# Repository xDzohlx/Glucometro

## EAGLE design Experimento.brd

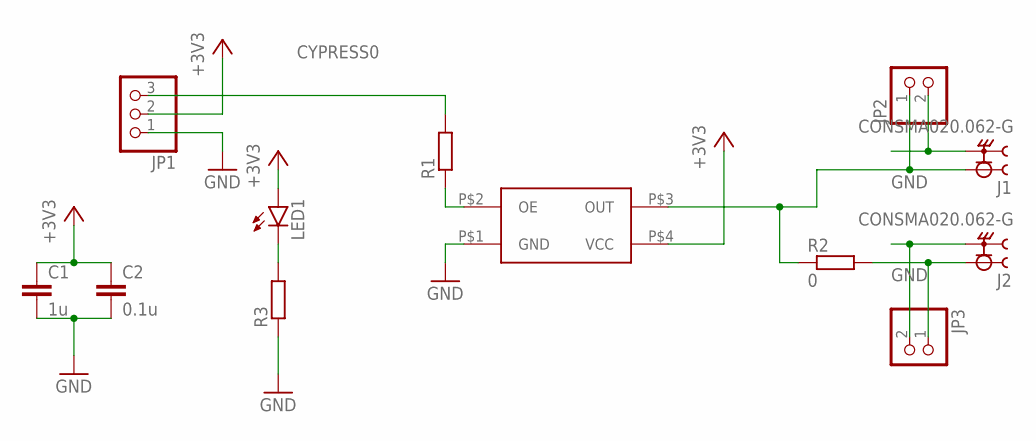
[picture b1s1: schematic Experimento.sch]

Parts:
C1: 1u; C0805
C2: 0.1u; C0805
J1, J2: CONSMA020.062-G; LINX_CONSMA020.062-G
JP1: PINHD-1X3; 1X03
JP2, JP3: PINHD-1X2M; 1X02M
LED1: LEDSML0603; SML0603
R1: R-EU_R0603; R0603
R2: 0; R1206
R3: R-EU_R0805; R0805
U$1: 732-XG1000CA100CBL3

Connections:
+3V3: C1.1, C2.1, JP1.2, LED1.A, U$1.P$4 (VCC)
CYPRESS0: JP1.3, R1.2
GND: C1.2, C2.2, J1.S1 (2), J1.S2 (2), J1.S3 (2), J1.S4 (2), J2.S1 (2), J2.S2 (2), J2.S3 (2), J2.S4 (2), JP1.1, JP2.2, JP3.2, R3.1, U$1.P$1 (GND)
unnamed: J2.1, JP3.1, R2.2
unnamed: LED1.C, R3.2
unnamed: R1.1, U$1.P$2 (OE)
SAW0: J1.1, JP2.1, R2.1, U$1.P$3 (OUT)

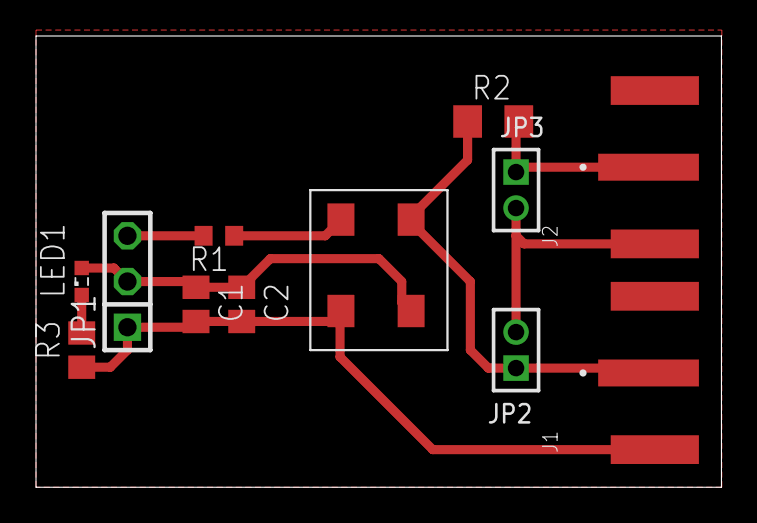
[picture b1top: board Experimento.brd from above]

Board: 2 copper layers, 38.1 x 25.1 mm, 12 parts (0 on the bottom side), 7 nets.
